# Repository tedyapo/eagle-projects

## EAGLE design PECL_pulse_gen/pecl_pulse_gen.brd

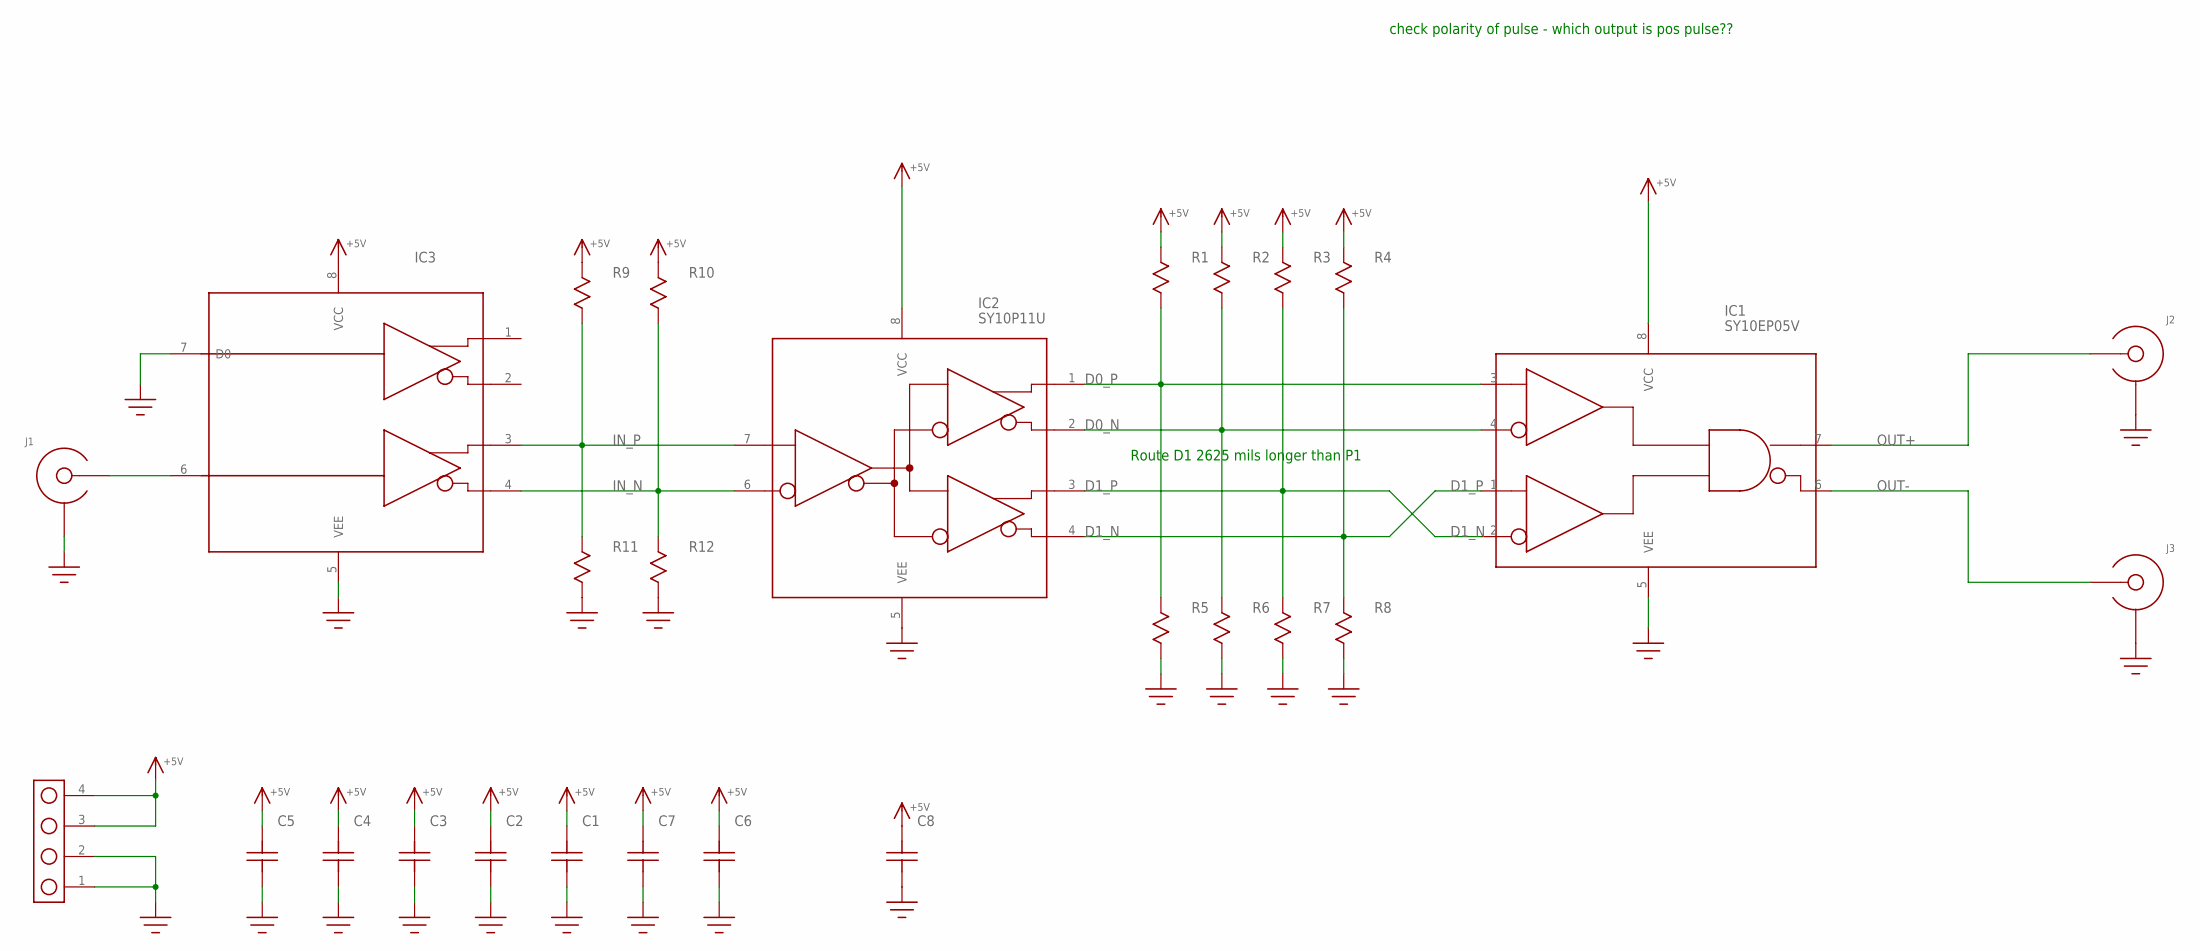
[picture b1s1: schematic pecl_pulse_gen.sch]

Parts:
C1, C2, C3, C4, C5, C6, C7: C0603
C8: C1206; 1206
IC1: SY10EP05V; SOIC8
IC2: SY10P11U; SOIC8
IC3: MC100LVELT22; SOIC8
J1, J2, J3: EDGE_LAUNCH_JACK; EDGE_LAUNCH_RF_CON
J4: HEADER_4PIN
R1, R2, R3, R4, R5, R6, R7, R8, R9, R10, R11, R12: R0402; 0402

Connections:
+5V: C1.P$2, C2.P$2, C3.P$2, C4.P$2, C5.P$2, C6.P$2, C7.P$2, C8.P$2, IC1.8 (VCC), IC2.8 (VCC), IC3.8 (VCC), J4.3, J4.4, R1.1, R2.1, R3.1, R4.1, R9.1, R10.1
D0_N: IC1.4 (!D1!), IC2.2 (!Q0!), R2.2, R6.1
D0_P: IC1.3 (D1), IC2.1 (Q0), R1.2, R5.1
D1_N: IC1.1 (D0), IC2.4 (!Q1!), R4.2, R8.1
D1_P: IC1.2 (!D0!), IC2.3 (Q1), R3.2, R7.1
GND: C1.P$1, C2.P$1, C3.P$1, C4.P$1, C5.P$1, C6.P$1, C7.P$1, C8.P$1, IC1.5 (VEE), IC2.5 (VEE), IC3.5 (VEE), IC3.7 (D0), J1.GND@1 (SHIELD), J1.GND@2 (SHIELD), J1.GND@3 (SHIELD), J1.GND@4 (SHIELD), J1.GND@5 (SHIELD), J1.GND@6 (SHIELD), J1.GND@7 (SHIELD), J1.GND@8 (SHIELD), J1.GND@9 (SHIELD), J1.GND@10 (SHIELD), J1.GND@11 (SHIELD), J1.GND@12 (SHIELD), J1.SHIELD@1 (SHIELD), J1.SHIELD@2 (SHIELD), J2.GND@1 (SHIELD), J2.GND@2 (SHIELD), J2.GND@3 (SHIELD), J2.GND@4 (SHIELD), J2.GND@5 (SHIELD), J2.GND@6 (SHIELD), J2.GND@7 (SHIELD), J2.GND@8 (SHIELD), J2.GND@9 (SHIELD), J2.GND@10 (SHIELD), J2.GND@11 (SHIELD), J2.GND@12 (SHIELD), J2.SHIELD@1 (SHIELD), J2.SHIELD@2 (SHIELD), J3.GND@1 (SHIELD), J3.GND@2 (SHIELD), J3.GND@3 (SHIELD), J3.GND@4 (SHIELD), J3.GND@5 (SHIELD), J3.GND@6 (SHIELD), J3.GND@7 (SHIELD), J3.GND@8 (SHIELD), J3.GND@9 (SHIELD), J3.GND@10 (SHIELD), J3.GND@11 (SHIELD), J3.GND@12 (SHIELD), J3.SHIELD@1 (SHIELD), J3.SHIELD@2 (SHIELD), J4.1, J4.2, R5.2, R6.2, R7.2, R8.2, R11.2, R12.2
IN_N: IC2.6 (!D!), IC3.4 (!Q1!), R10.2, R12.1
IN_P: IC2.7 (D), IC3.3 (Q1), R9.2, R11.1
unnamed: IC3.6 (D1), J1.CENTER
OUT+: IC1.7 (Q), J2.CENTER
OUT-: IC1.6 (!Q!), J3.CENTER

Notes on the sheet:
check polarity of pulse - which output is pos pulse??
Route D1 2625 mils longer than P1

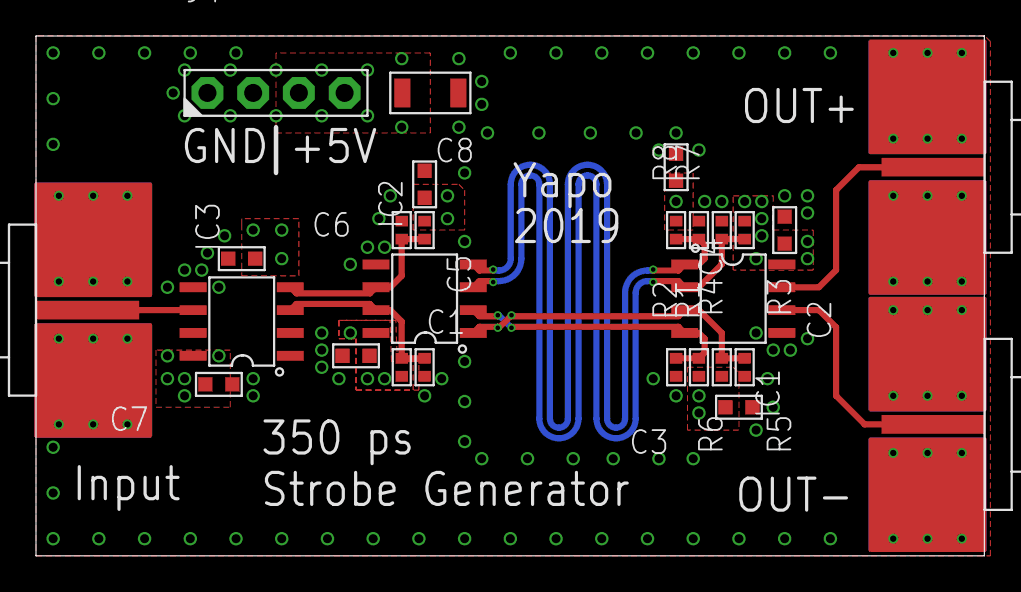
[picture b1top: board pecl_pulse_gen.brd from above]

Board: 4 copper layers, 52.7 x 28.9 mm, 27 parts (0 on the bottom side), 11 nets.

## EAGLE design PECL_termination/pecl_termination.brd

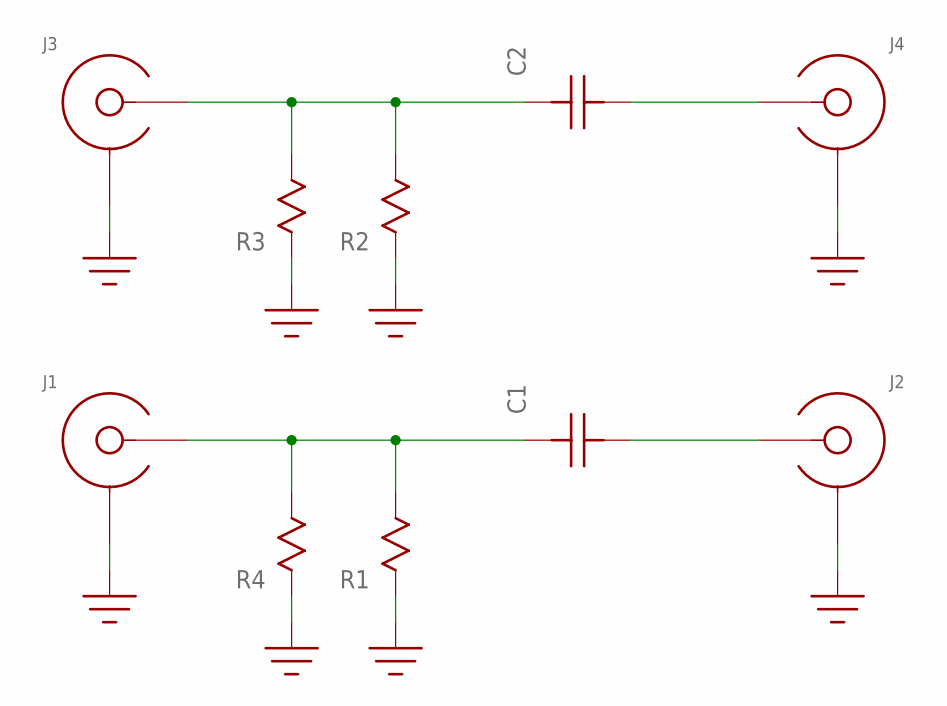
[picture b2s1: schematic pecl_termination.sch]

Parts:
C1, C2: C0805; 0805
J1, J2, J3, J4: EDGE_LAUNCH_JACK; EDGE_LAUNCH_RF_CON
R1, R2, R3, R4: R0805

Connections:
GND: J1.GND@1 (SHIELD), J1.GND@2 (SHIELD), J1.GND@3 (SHIELD), J1.GND@4 (SHIELD), J1.GND@5 (SHIELD), J1.GND@6 (SHIELD), J1.GND@7 (SHIELD), J1.GND@8 (SHIELD), J1.GND@9 (SHIELD), J1.GND@10 (SHIELD), J1.GND@11 (SHIELD), J1.GND@12 (SHIELD), J1.SHIELD@1 (SHIELD), J1.SHIELD@2 (SHIELD), J2.GND@1 (SHIELD), J2.GND@2 (SHIELD), J2.GND@3 (SHIELD), J2.GND@4 (SHIELD), J2.GND@5 (SHIELD), J2.GND@6 (SHIELD), J2.GND@7 (SHIELD), J2.GND@8 (SHIELD), J2.GND@9 (SHIELD), J2.GND@10 (SHIELD), J2.GND@11 (SHIELD), J2.GND@12 (SHIELD), J2.SHIELD@1 (SHIELD), J2.SHIELD@2 (SHIELD), J3.GND@1 (SHIELD), J3.GND@2 (SHIELD), J3.GND@3 (SHIELD), J3.GND@4 (SHIELD), J3.GND@5 (SHIELD), J3.GND@6 (SHIELD), J3.GND@7 (SHIELD), J3.GND@8 (SHIELD), J3.GND@9 (SHIELD), J3.GND@10 (SHIELD), J3.GND@11 (SHIELD), J3.GND@12 (SHIELD), J3.SHIELD@1 (SHIELD), J3.SHIELD@2 (SHIELD), J4.GND@1 (SHIELD), J4.GND@2 (SHIELD), J4.GND@3 (SHIELD), J4.GND@4 (SHIELD), J4.GND@5 (SHIELD), J4.GND@6 (SHIELD), J4.GND@7 (SHIELD), J4.GND@8 (SHIELD), J4.GND@9 (SHIELD), J4.GND@10 (SHIELD), J4.GND@11 (SHIELD), J4.GND@12 (SHIELD), J4.SHIELD@1 (SHIELD), J4.SHIELD@2 (SHIELD), R1.P$1, R2.P$1, R3.P$1, R4.P$1
unnamed: C1.P$2, J1.CENTER, R1.P$2, R4.P$2
unnamed: C1.P$1, J2.CENTER
unnamed: C2.P$2, J3.CENTER, R2.P$2, R3.P$2
unnamed: C2.P$1, J4.CENTER

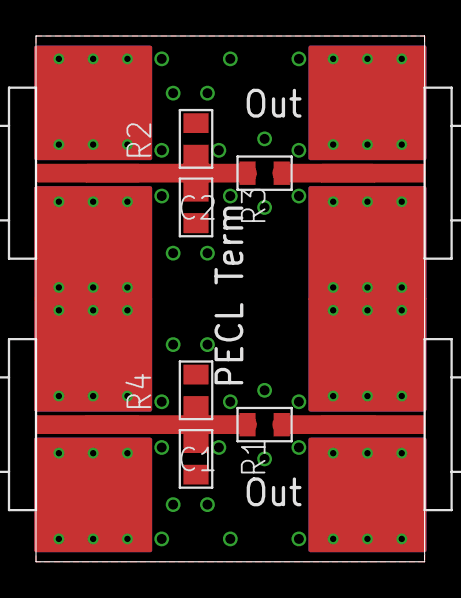
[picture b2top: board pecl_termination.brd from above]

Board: 2 copper layers, 21.6 x 29.2 mm, 10 parts (0 on the bottom side), 5 nets.

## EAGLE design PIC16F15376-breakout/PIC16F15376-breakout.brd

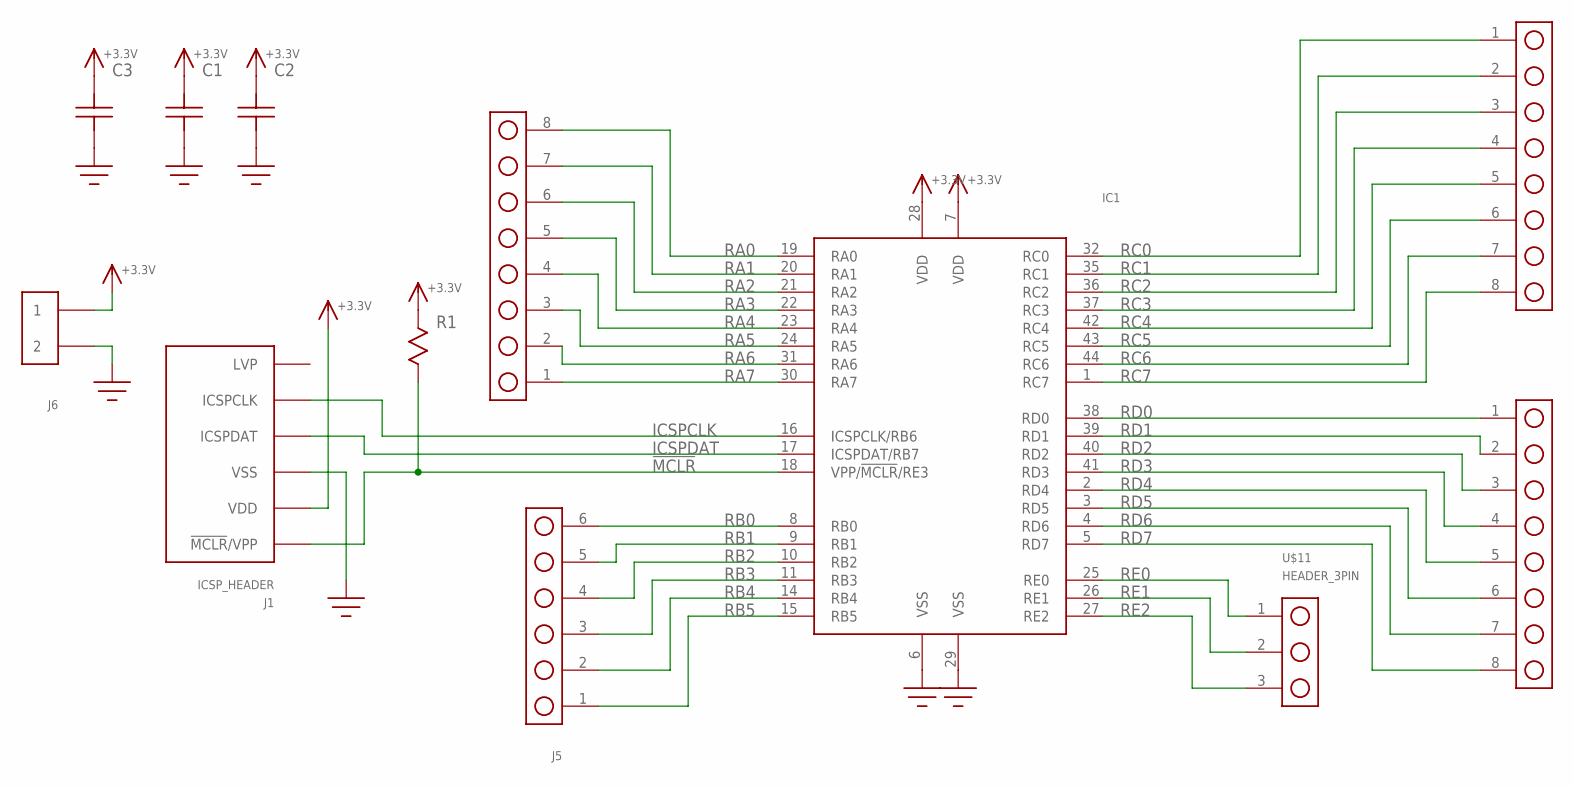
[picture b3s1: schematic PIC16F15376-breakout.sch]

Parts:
C1, C2: C0603
C3: C1206; 1206
IC1: PIC16F15376; TQFP44
J1: ICSP_HEADER; HEADER_6PIN
J2, J3, J4: HEADER_8PIN; HEADER_8_PIN
J5: HEADER_6PIN
J6: HEADER_2PIN
R1: R0603
U$11: HEADER_3PIN

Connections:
!MCLR!: IC1.18 (VPP/!MCLR!/RE3), J1.1 (!MCLR!/VPP), R1.P$2
+3.3V: C1.P$2, C2.P$2, C3.P$2, IC1.7 (VDD), IC1.28 (VDD), J1.2 (VDD), J6.1, R1.P$1
GND: C1.P$1, C2.P$1, C3.P$1, IC1.6 (VSS), IC1.29 (VSS), J1.3 (VSS), J6.2
ICSPCLK: IC1.16 (ICSPCLK/RB6), J1.5 (ICSPCLK)
ICSPDAT: IC1.17 (ICSPDAT/RB7), J1.4 (ICSPDAT)
RA0: IC1.19 (RA0), J2.8
RA1: IC1.20 (RA1), J2.7
RA2: IC1.21 (RA2), J2.6
RA3: IC1.22 (RA3), J2.5
RA4: IC1.23 (RA4), J2.4
RA5: IC1.24 (RA5), J2.3
RA6: IC1.31 (RA6), J2.2
RA7: IC1.30 (RA7), J2.1
RB0: IC1.8 (RB0), J5.6
RB1: IC1.9 (RB1), J5.5
RB2: IC1.10 (RB2), J5.4
RB3: IC1.11 (RB3), J5.3
RB4: IC1.14 (RB4), J5.2
RB5: IC1.15 (RB5), J5.1
RC0: IC1.32 (RC0), J3.1
RC1: IC1.35 (RC1), J3.2
RC2: IC1.36 (RC2), J3.3
RC3: IC1.37 (RC3), J3.4
RC4: IC1.42 (RC4), J3.5
RC5: IC1.43 (RC5), J3.6
RC6: IC1.44 (RC6), J3.7
RC7: IC1.1 (RC7), J3.8
RD0: IC1.38 (RD0), J4.1
RD1: IC1.39 (RD1), J4.2
RD2: IC1.40 (RD2), J4.3
RD3: IC1.41 (RD3), J4.4
RD4: IC1.2 (RD4), J4.5
RD5: IC1.3 (RD5), J4.6
RD6: IC1.4 (RD6), J4.7
RD7: IC1.5 (RD7), J4.8
RE0: IC1.25 (RE0), U$11.1
RE1: IC1.26 (RE1), U$11.2
RE2: IC1.27 (RE2), U$11.3

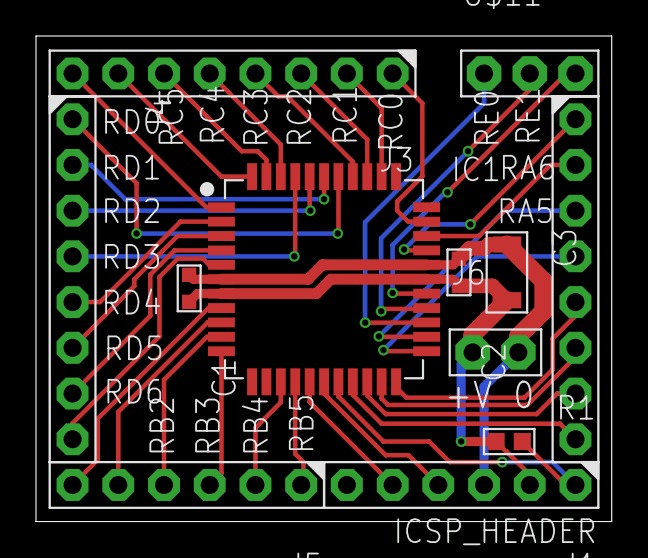
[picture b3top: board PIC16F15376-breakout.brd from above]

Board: 2 copper layers, 32.0 x 27.0 mm, 12 parts (0 on the bottom side), 38 nets.

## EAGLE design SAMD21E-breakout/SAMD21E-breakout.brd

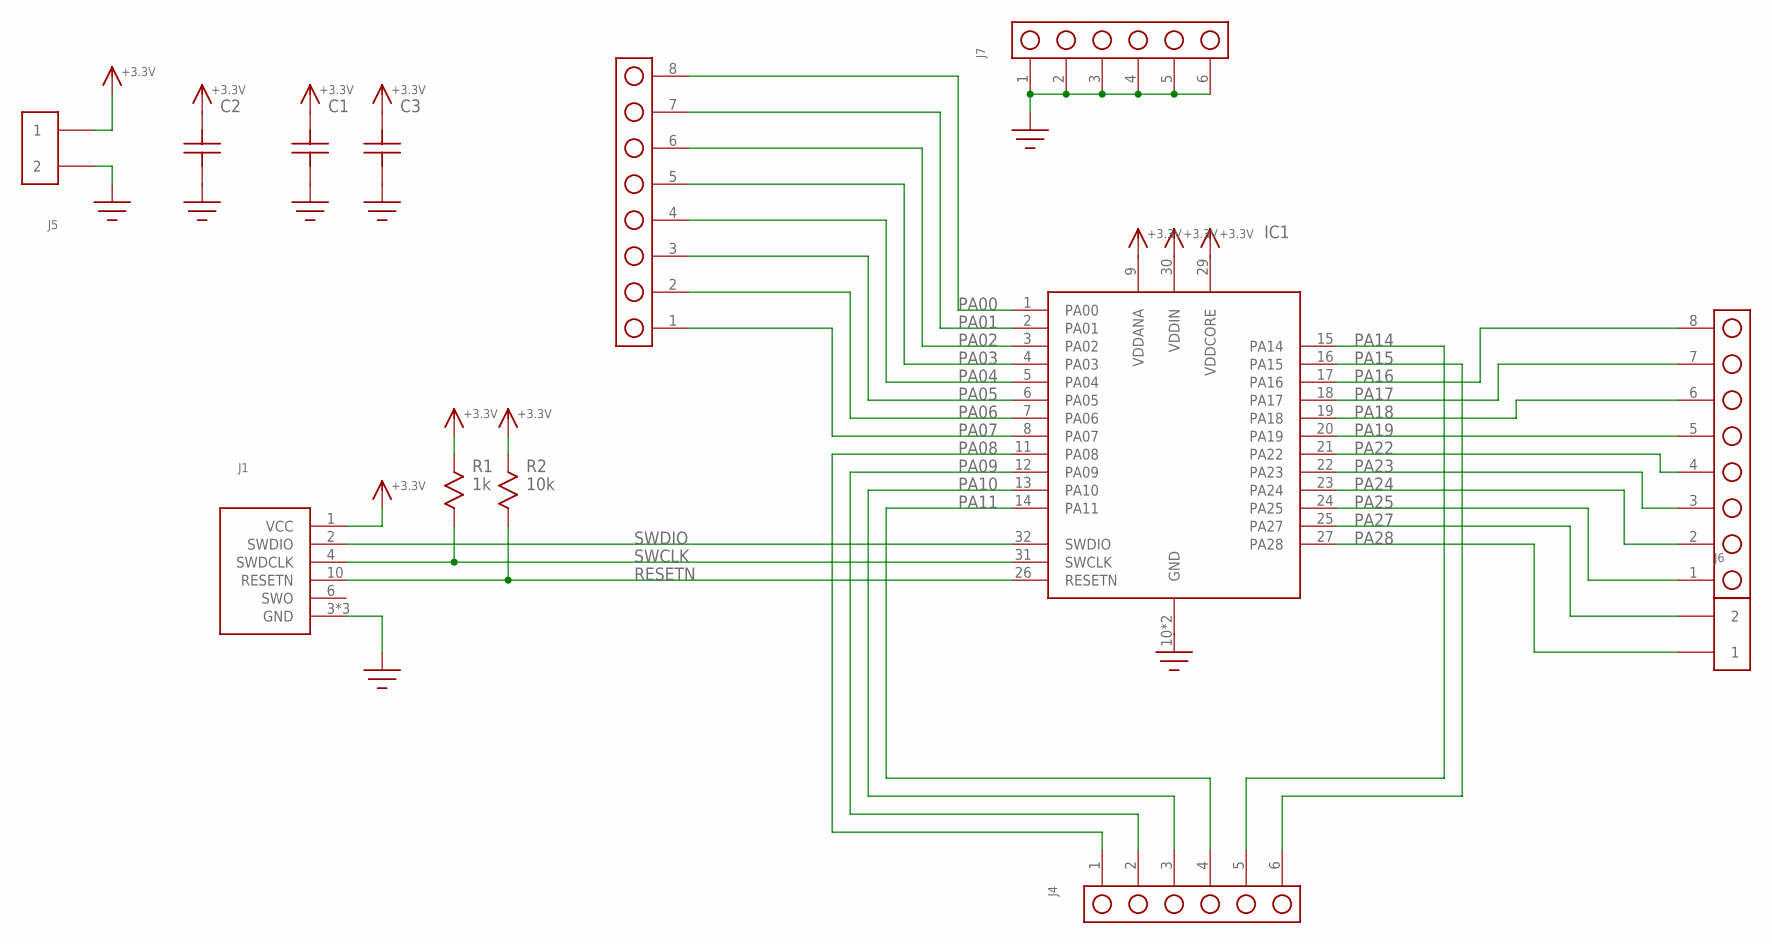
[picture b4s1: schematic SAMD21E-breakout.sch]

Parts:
C1, C3: C0603
C2: C1206; 1206
IC1: SAMD21E; TQFP32_7X7
J1: SWD-ICSP-HEADER; HEADER-2X5-50MIL
J2, J3: HEADER_8PIN; HEADER_8_PIN
J4, J7: HEADER_6PIN
J5, J6: HEADER_2PIN
R1: 1k; R0603
R2: 10k; R0603

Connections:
+3.3V: C1.P$2, C2.P$2, C3.P$2, IC1.9 (VDDANA), IC1.29 (VDDCORE), IC1.30 (VDDIN), J1.1 (VCC), J5.1, R1.P$1, R2.P$1
GND: C1.P$1, C2.P$1, C3.P$1, IC1.10 (GND), IC1.28 (GND), J1.3 (GND), J1.5 (GND), J1.9 (GND), J5.2, J7.1, J7.2, J7.3, J7.4, J7.5, J7.6
PA00: IC1.1 (PA00), J2.8
PA01: IC1.2 (PA01), J2.7
PA02: IC1.3 (PA02), J2.6
PA03: IC1.4 (PA03), J2.5
PA04: IC1.5 (PA04), J2.4
PA05: IC1.6 (PA05), J2.3
PA06: IC1.7 (PA06), J2.2
PA07: IC1.8 (PA07), J2.1
PA08: IC1.11 (PA08), J4.1
PA09: IC1.12 (PA09), J4.2
PA10: IC1.13 (PA10), J4.3
PA11: IC1.14 (PA11), J4.4
PA14: IC1.15 (PA14), J4.5
PA15: IC1.16 (PA15), J4.6
PA16: IC1.17 (PA16), J3.8
PA17: IC1.18 (PA17), J3.7
PA18: IC1.19 (PA18), J3.6
PA19: IC1.20 (PA19), J3.5
PA22: IC1.21 (PA22), J3.4
PA23: IC1.22 (PA23), J3.3
PA24: IC1.23 (PA24), J3.2
PA25: IC1.24 (PA25), J3.1
PA27: IC1.25 (PA27), J6.2
PA28: IC1.27 (PA28), J6.1
RESETN: IC1.26 (RESETN), J1.10 (RESETN), R2.P$2
SWCLK: IC1.31 (SWCLK), J1.4 (SWDCLK), R1.P$2
SWDIO: IC1.32 (SWDIO), J1.2 (SWDIO)

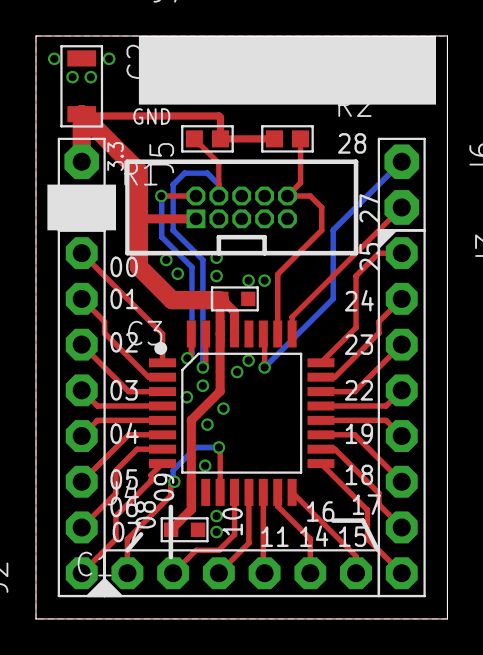
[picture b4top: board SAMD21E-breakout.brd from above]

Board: 2 copper layers, 22.9 x 32.4 mm, 13 parts (0 on the bottom side), 29 nets.

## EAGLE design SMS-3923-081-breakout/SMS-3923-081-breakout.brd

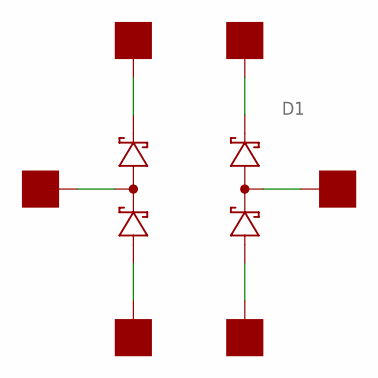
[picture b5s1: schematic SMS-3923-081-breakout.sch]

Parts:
D1: SMS3923-081; SC-88
U$1, U$2, U$3, U$4, U$5, U$6: PAD50MIL; PAD_50MIL

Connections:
unnamed: D1.4 (CATHODE1), U$2.P$1
unnamed: D1.3 (CATHODE0), U$1.P$1
unnamed: D1.2 (COMMON0), U$5.P$1
unnamed: D1.1 (ANODE0), U$4.P$1
unnamed: D1.6 (ANODE1), U$3.P$1
unnamed: D1.5 (COMMON1), U$6.P$1

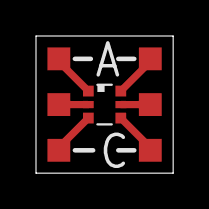
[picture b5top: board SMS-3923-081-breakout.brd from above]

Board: 2 copper layers, 7.6 x 7.6 mm, 7 parts (0 on the bottom side), 6 nets.

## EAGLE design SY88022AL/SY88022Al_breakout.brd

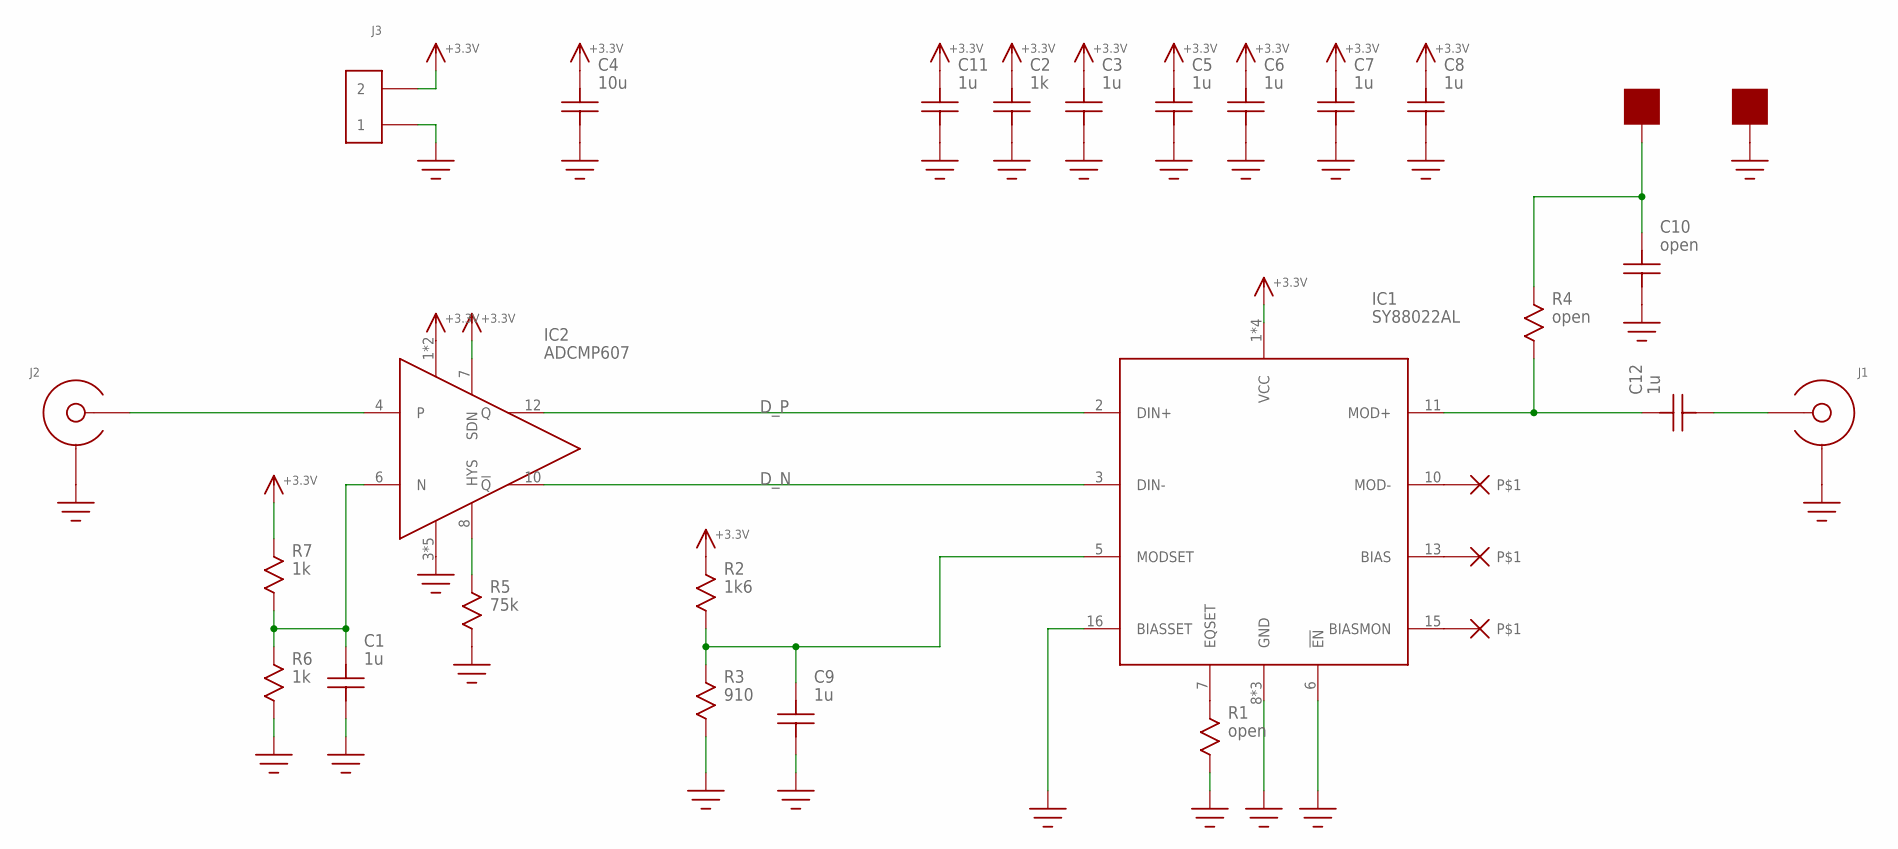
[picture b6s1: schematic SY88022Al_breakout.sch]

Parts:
C1, C3, C5, C6, C7, C8, C9, C11, C12: 1u; C0603
C2: 1k; C0603
C4: 10u; 1206
C10: open; C0603
IC1: SY88022AL; TQFN16-EP
IC2: ADCMP607; QFN12-3X3
J1, J2: EDGE_LAUNCH_JACKNARROW; EDGE_LAUNCH_RF_CON_NARROW
J3: HEADER_2PIN
R1: open; 0402
R2: 1k6; R0603
R3: 910; R0603
R4: open; R0603
R5: 75k; R0603
R6, R7: 1k; R0603
U$29, U$36: PAD100MIL; PAD_100MIL

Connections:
+3.3V: C2.P$2, C3.P$2, C4.P$2, C5.P$2, C6.P$2, C7.P$2, C8.P$2, C11.P$2, IC1.1 (VCC), IC1.4 (VCC), IC1.9 (VCC), IC1.12 (VCC), IC2.1 (VCC), IC2.2 (VCC), IC2.7 (SDN), J3.2, R2.P$1, R7.P$1
D_N: IC1.3 (DIN-), IC2.10 (!Q!)
D_P: IC1.2 (DIN+), IC2.12 (Q)
GND: C1.P$1, C2.P$1, C3.P$1, C4.P$1, C5.P$1, C6.P$1, C7.P$1, C8.P$1, C9.P$1, C10.P$1, C11.P$1, IC1.6 (!EN!), IC1.8 (GND), IC1.14 (GND), IC1.16 (BIASSET), IC1.EP (GND), IC2.3 (VEE), IC2.5 (VEE), IC2.9 (VEE), IC2.11 (VEE), IC2.EP (VEE), J1.GND@1 (SHIELD), J1.GND@2 (SHIELD), J1.GND@3 (SHIELD), J1.GND@4 (SHIELD), J1.GND@5 (SHIELD), J1.GND@6 (SHIELD), J1.SHIELD@1 (SHIELD), J1.SHIELD@2 (SHIELD), J2.GND@1 (SHIELD), J2.GND@2 (SHIELD), J2.GND@3 (SHIELD), J2.GND@4 (SHIELD), J2.GND@5 (SHIELD), J2.GND@6 (SHIELD), J2.SHIELD@1 (SHIELD), J2.SHIELD@2 (SHIELD), J3.1, R1.2, R3.P$2, R5.P$2, R6.P$2, U$36.P$1
unnamed: IC1.7 (EQSET), R1.1
unnamed: C9.P$2, IC1.5 (MODSET), R2.P$2, R3.P$1
unnamed: C12.P$1, J1.CENTER
unnamed: C12.P$2, IC1.11 (MOD+), R4.P$2
unnamed: C10.P$2, R4.P$1, U$29.P$1
unnamed: IC2.8 (HYS), R5.P$1
unnamed: C1.P$2, IC2.6 (N), R6.P$1, R7.P$2
unnamed: IC2.4, J2.CENTER

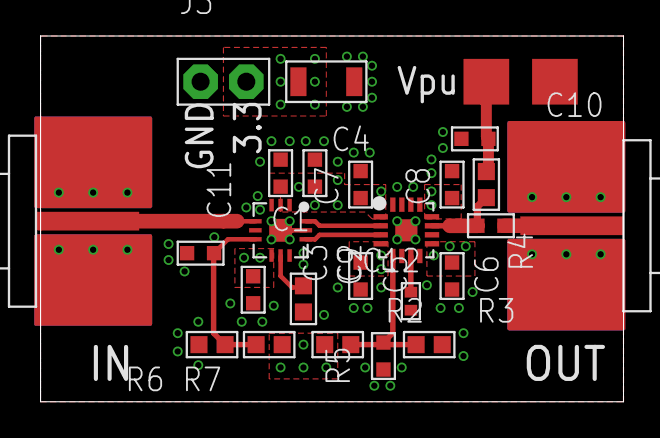
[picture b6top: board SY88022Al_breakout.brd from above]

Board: 4 copper layers, 32.4 x 20.3 mm, 26 parts (0 on the bottom side), 12 nets.

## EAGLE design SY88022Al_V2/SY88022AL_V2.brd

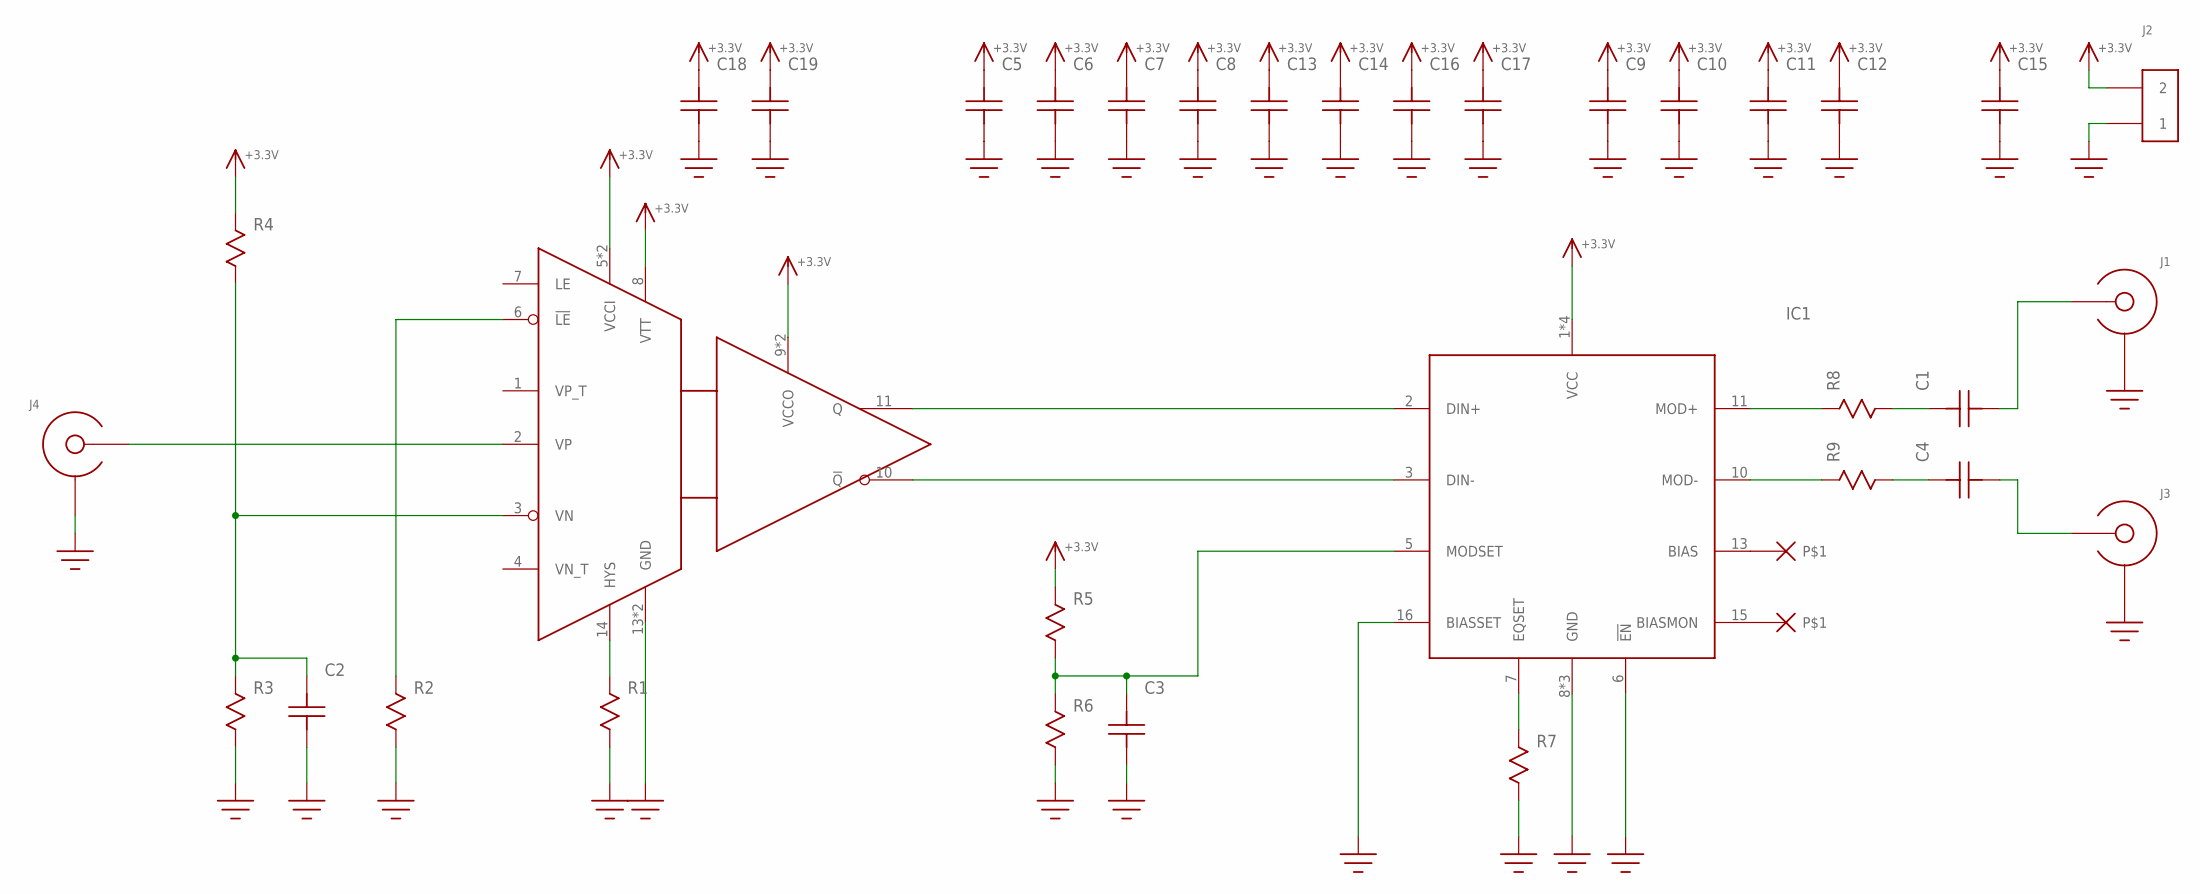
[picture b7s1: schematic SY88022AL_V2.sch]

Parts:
C1, C4, C5, C6, C7, C8, C13, C14, C16, C17: C; C0402
C2, C3, C9, C10, C11, C12: C0603
C15: C1206; 1206
C18, C19: C0201; 0201
IC1: SY88022AL; TQFN16-EP
J1, J3, J4: SMA_END_LAUNCH4L; SMA_EDGE_LAUNCH
J2: HEADER_2PIN
R1, R2, R3, R4, R5, R6, R7: R0603
R8, R9: R0402; 0402
U$1: ADCMP572; TQFN16-EP

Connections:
+3.3V: C5.2, C6.2, C7.2, C8.2, C9.P$2, C10.P$2, C11.P$2, C12.P$2, C13.2, C14.2, C15.P$2, C16.2, C17.2, C18.P$2, C19.P$2, IC1.1 (VCC), IC1.4 (VCC), IC1.9 (VCC), IC1.12 (VCC), J2.2, R4.P$1, R5.P$1, U$1.5 (VCCI), U$1.8 (VTT), U$1.9 (VCCO), U$1.12 (VCCO), U$1.16 (VCCI)
GND: C2.P$1, C3.P$1, C5.1, C6.1, C7.1, C8.1, C9.P$1, C10.P$1, C11.P$1, C12.P$1, C13.1, C14.1, C15.P$1, C16.1, C17.1, C18.P$1, C19.P$1, IC1.6 (!EN!), IC1.8 (GND), IC1.14 (GND), IC1.16 (BIASSET), IC1.EP (GND), J1.BOTTOM_PAD (SHIELD), J1.GND@1 (SHIELD), J1.GND@2 (SHIELD), J1.GND@3 (SHIELD), J1.GND@4 (SHIELD), J1.GND@5 (SHIELD), J1.GND@6 (SHIELD), J1.GND@7 (SHIELD), J1.GND@8 (SHIELD), J1.GND@14 (SHIELD), J1.GND@15 (SHIELD), J1.GND@16 (SHIELD), J1.GND@17 (SHIELD), J1.GND_PAD1 (SHIELD), J1.GND_PAD2 (SHIELD), J2.1, J3.BOTTOM_PAD (SHIELD), J3.GND@1 (SHIELD), J3.GND@2 (SHIELD), J3.GND@3 (SHIELD), J3.GND@4 (SHIELD), J3.GND@5 (SHIELD), J3.GND@6 (SHIELD), J3.GND@7 (SHIELD), J3.GND@8 (SHIELD), J3.GND@14 (SHIELD), J3.GND@15 (SHIELD), J3.GND@16 (SHIELD), J3.GND@17 (SHIELD), J3.GND_PAD1 (SHIELD), J3.GND_PAD2 (SHIELD), J4.BOTTOM_PAD (SHIELD), J4.GND@1 (SHIELD), J4.GND@2 (SHIELD), J4.GND@3 (SHIELD), J4.GND@4 (SHIELD), J4.GND@5 (SHIELD), J4.GND@6 (SHIELD), J4.GND@7 (SHIELD), J4.GND@8 (SHIELD), J4.GND@14 (SHIELD), J4.GND@15 (SHIELD), J4.GND@16 (SHIELD), J4.GND@17 (SHIELD), J4.GND_PAD1 (SHIELD), J4.GND_PAD2 (SHIELD), R1.P$2, R2.P$2, R3.P$2, R6.P$2, R7.P$2, U$1.13 (GND), U$1.15 (GND)
unnamed: IC1.2 (DIN+), U$1.11 (Q)
unnamed: IC1.3 (DIN-), U$1.10 (!Q!)
unnamed: R1.P$1, U$1.14 (HYS)
unnamed: R2.P$1, U$1.6 (!LE!)
unnamed: C2.P$2, R3.P$1, R4.P$2, U$1.3 (VN)
unnamed: J4.CENTER@1 (CENTER), J4.CENTER@2 (CENTER), U$1.2 (VP)
unnamed: C3.P$2, IC1.5 (MODSET), R5.P$2, R6.P$1
unnamed: C1.2, R8.2
unnamed: IC1.7 (EQSET), R7.P$1
unnamed: IC1.11 (MOD+), R8.1
unnamed: IC1.10 (MOD-), R9.1
unnamed: C4.2, R9.2
unnamed: C1.1, J1.CENTER@1 (CENTER), J1.CENTER@2 (CENTER)
unnamed: C4.1, J3.CENTER@1 (CENTER), J3.CENTER@2 (CENTER)

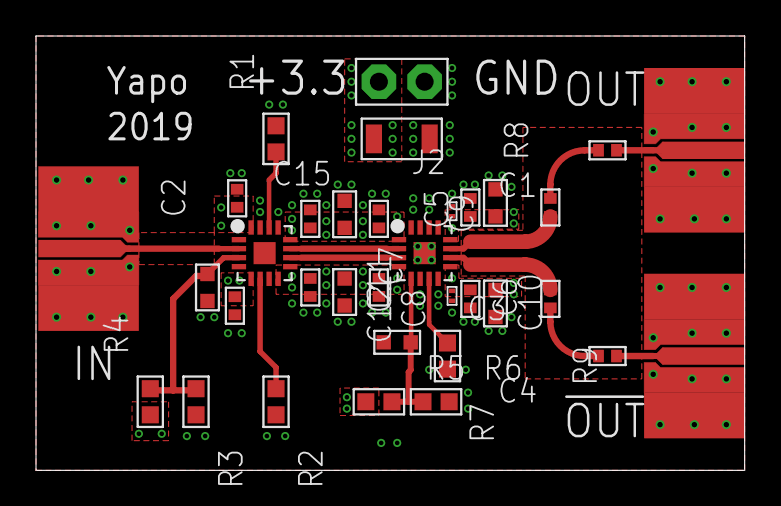
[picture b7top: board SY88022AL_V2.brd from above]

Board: 4 copper layers, 39.4 x 24.1 mm, 34 parts (0 on the bottom side), 16 nets.

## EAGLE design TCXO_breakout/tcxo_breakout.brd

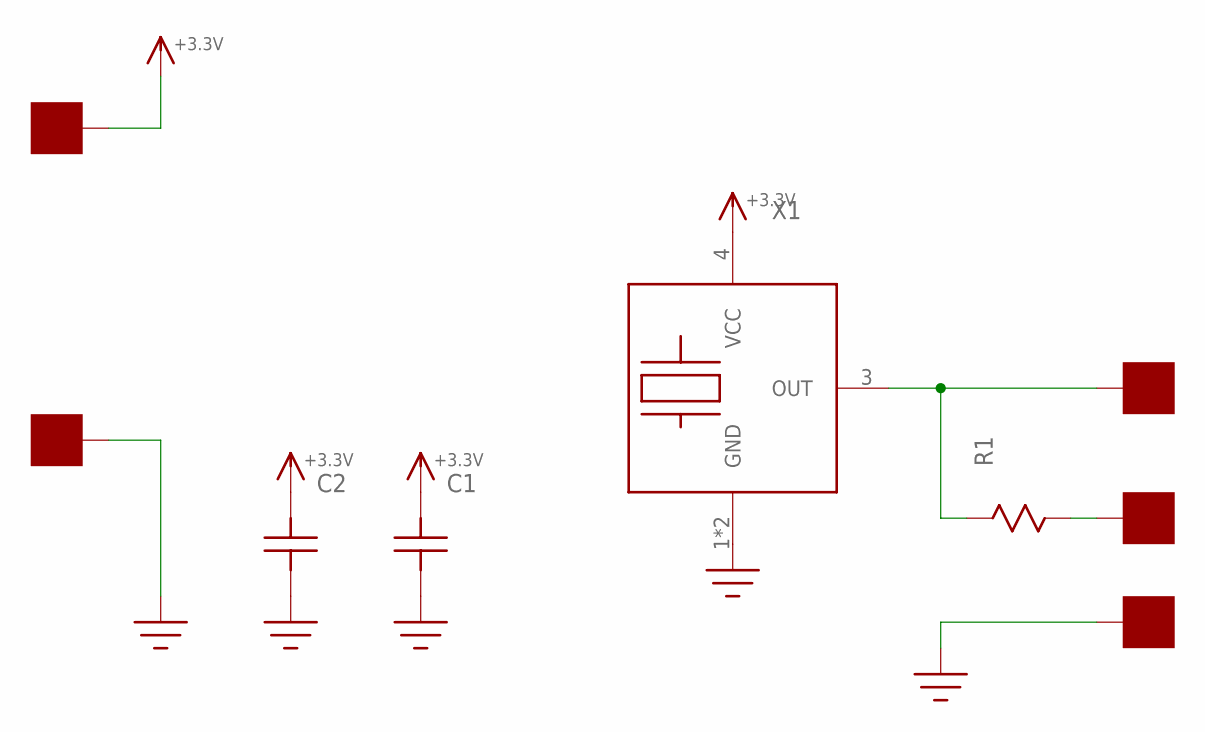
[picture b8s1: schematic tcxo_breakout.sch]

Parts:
C1: C0603
C2: C0805; 0805
R1: R0603
U$1, U$2, U$3, U$12, U$13: PAD100MIL; PAD_100MIL
X1: XTAL_OSC3.2X2.5; XTAL_3.2X2.5

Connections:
+3.3V: C1.P$2, C2.P$2, U$1.P$1, X1.4 (VCC)
GND: C1.P$1, C2.P$1, U$2.P$1, U$13.P$1, X1.1 (GND), X1.2 (GND)
unnamed: R1.P$1, U$3.P$1, X1.3 (OUT)
unnamed: R1.P$2, U$12.P$1

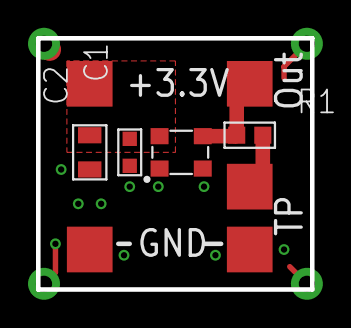
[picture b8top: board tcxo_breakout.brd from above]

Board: 2 copper layers, 15.2 x 14.0 mm, 9 parts (0 on the bottom side), 4 nets.
